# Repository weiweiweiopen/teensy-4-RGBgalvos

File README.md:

# teensy-4-RGBgalvos

Teensy 4.0 + CS42448 的 **8 通道 USB 音訊 → TDM → 8 組差分 ILDA 類比輸出**控制板。
本 repo 是目前 **RevB-P4** 設計的交接包：KiCad 專案、分析證據、製造檔、韌體與量測指南。

> 這是**可打樣、但尚未實板驗證**的版本。製造放行仍是 HOLD，請先讀 [交接總覽](docs/00-交接總覽-zhTW.md)。

## 30 秒狀態

| 項目 | 狀態 |
|---|---|
| 設計版本 | RevB-P4（110 × 100 mm、4 層、1.6 mm、337 footprints、316 SMT） |
| PCB SHA-256 | `825edcd27853183ae879091047c481432507c4003eede9e3af0c213e0eff5e42` |
| 原生檢查 | DRC 0 / unconnected 0 / ERC 0 / parity 0（另有 2 個既有 J1 絲印 warning） |
| Gerber/drill | 已回讀：545 鑽孔、1,031 unique ref/pin、14 檔 ZIP |
| 製造 | **HOLD**：U1 CS42448 缺料、DB25 實際料號、JLC 貼裝角度、實板驗證 |
| 韌體 | 已編譯、**未燒錄**；預設 gain 0.70、offset 0、未校正 |

## 從哪裡開始

| 你要做的事 | 先讀 |
|---|---|
| 5 分鐘了解整體 | [docs/00-交接總覽](docs/00-交接總覽-zhTW.md) |
| 看懂電路與訊號 | [docs/01-訊號鏈](docs/01-訊號鏈-zhTW.md) |
| 第一次上電 | [docs/02-上電與測試](docs/02-上電與測試-zhTW.md) |
| 校正八通道 | [docs/03-校正](docs/03-校正-zhTW.md) |
| 送 JLC 打樣 | [docs/04-製造與供料](docs/04-製造與供料-zhTW.md) |
| 改／燒韌體 | [docs/05-韌體](docs/05-韌體-zhTW.md) |
| 找檔案與雜湊 | [docs/06-檔案地圖](docs/06-檔案地圖-zhTW.md) |

## 專案來源與授權

- **韌體核心**：改自 [alex6679/teensy-4-usbAudio](https://github.com/alex6679/teensy-4-usbAudio)（MIT），加上 Teensyduino 1.59 的 UAC2 8 通道 patch。原始授權與出處見 [docs/05-韌體](docs/05-韌體-zhTW.md)。
- **硬體架構規劃**：由使用者以 **GPT Sol 6.1** 規劃（電源順序、隔離、watchdog、ILDA 介面）。本 repo 的 KiCad、ECO、分析與製造檔是該規劃的實作與驗證結果。
- **介面標準**：ILDA ISP-DB25 rev002（1999）：DB25 母座、X/Y 差分 10 Vpp、R/G/B/I 差分 5 Vpp、Shutter 0/+5 V、Interlock 迴路。
- **本 repo 授權**：MIT，見 [`LICENSE`](LICENSE)。datasheet、廠商圖與量測原始檔不隨 repo 散布。

## 目錄

- `hardware/revB/` — 現行設計（KiCad、分析、製造、韌體）
- `hardware/revA/` — 前一版，保留比對用
- `firmware/` — 共用 Teensy USB audio core 與早期測試 sketch
- `kicad/`、`python/` — 早期公開的概略電路與雷射路徑工具（本次未變動）
- `docs/` — 中文交接文件
- `FIRMWARE-PINS.json` — 硬體／韌體腳位對照

## 重要警告

1. 本設計**沒有**實板電源 ramp、漏電、精度、線材穩定度、滿載熱、EMC 或 USB 合規測試。分析通過不等於電氣合格。
2. `calibration.h` 的 gain/offset 是預設值，不是量測結果。
3. **預設 gain 0.70 對 X/Y 安全，對顏色超幅約 1.77 倍**：顏色應降到 0.35–0.394。詳見 [docs/03-校正](docs/03-校正-zhTW.md)。
4. 韌體有一個已知缺陷：ch ≥ 2（R/G/B/I）在加 offset 前就把負值截為 0，負向零點無法補償。詳見 [docs/03-校正](docs/03-校正-zhTW.md)。
5. 本板輸出**直接驅動 ILDA 投影機**；上電測試請用限流電源、先不接雷射、確認 interlock 與 shutter 行為。

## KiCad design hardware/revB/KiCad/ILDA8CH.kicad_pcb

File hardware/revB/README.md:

# RevB-P4：電氣保護與供電恢復ECO

**目前主工程：337 footprints、316 SMT、110×100mm、4層。** 原273個元件擺件保留；新增隔離、監測與控制電路。Native unconnected／DRC errors／ERC／parity均0，完整依據見[ECO審查](QA/power-eco-review.md)。

**製造放行仍為HOLD：J1實際MPN／機構、CS42448供料、JLC裝配角度尚待完成。** 製造資料以`manufacturing/`最新ECO draft receipt為準。

- [KiCad工程](KiCad/ILDA8CH.kicad_pro)／[PCB](KiCad/ILDA8CH.kicad_pcb)
- [原生DRC](QA/routing-drc.json)／[ERC](QA/erc.json)／[完整一致性與局部路徑audit](QA/power-eco-audit.json)
- [RevB韌體](firmware/ilda8ch_revB/ilda8ch_revB.ino)：八路USB/TDM已編譯、未燒錄。GPIO5=status、GPIO6=fresh ARM；active stop同時assert codec RESET。
- [電氣模型與邏輯回歸](QA/power-eco-verification.json)
- 新版原生preview以`preview/power-eco-*`檔為準；舊P3擺件／桌面截圖是歷史。

## 電氣修正

C18=22µF→FILT_ADC；C20=100µF→FILT_DAC。U31–U34隔開16個DAC輸入，原100k與濾波增益保留、OPA輸入新增10M回地。U35/U10依實際MCU3V3隔離ADC，上游100nF與下游4.7k配合新版27.2766／32.2766係數。U6推挽雙軌資格、U7 reset gate、U8 fresh-edge latch、U37 Schmitt shutter OE與較強下拉共同處理掉電／恢復。

In1專用GND；In2保留GND並有ECO跨接，總trace長約1938.358mm，不是純GND。native規則未降低，無新增exclusion。數值／pin-function依據不等於實板ramp、精密DC或EMC合格。

## 編輯與歷史

主PCB SHA-256：`19c24b7b0cacdd23822d85daa3e44d5104a866f5a9f83ac38824fee33554cd69`。`sources/electrical.json`／`placement.json`已同步；local symbols／footprints與datasheets隨工程。已有走線，`build_placement.py`的舊placement receipt guard刻意保留，不應直接重建覆蓋。

修正前完整快照及各輪工作證據在`eco/power-sequencing-20261025/`；P1/P2/P3與先前preflight仍保留。原始硬體及RevA是歷史入口。

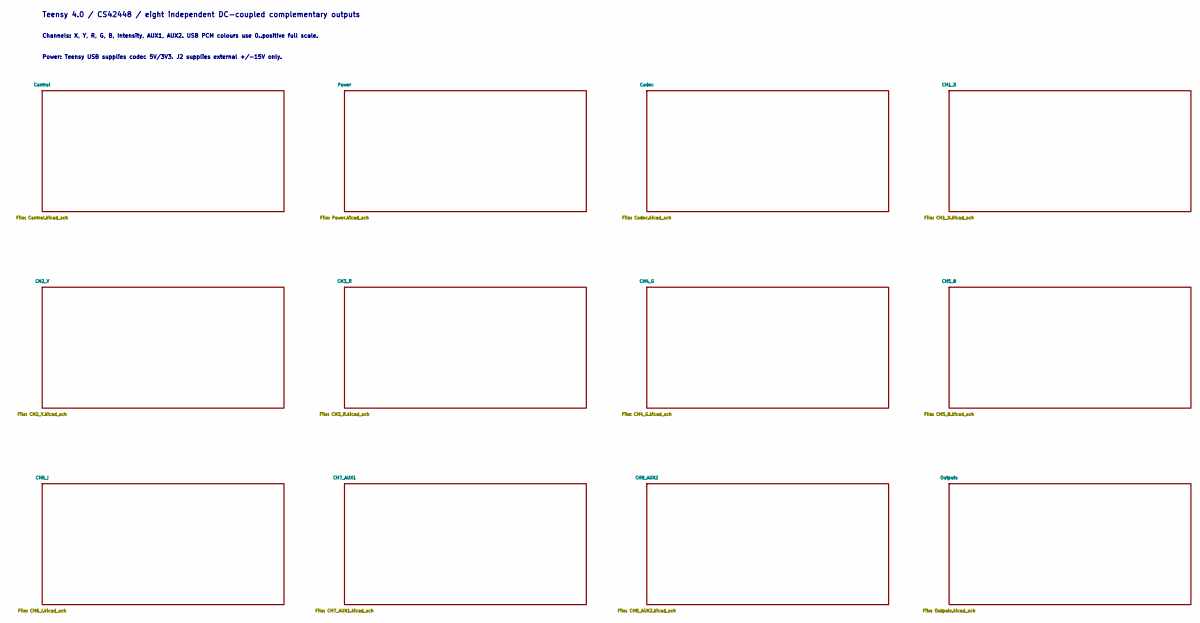
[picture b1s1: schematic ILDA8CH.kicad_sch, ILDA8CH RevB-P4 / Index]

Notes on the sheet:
Channels: X, Y, R, G, B, Intensity, AUX1, AUX2. USB PCM colours use 0..positive full scale.
Teensy 4.0 / CS42448 / eight independent DC-coupled complementary outputs
Power: Teensy USB supplies codec 5V/3V3. J2 supplies external +/-15V only.

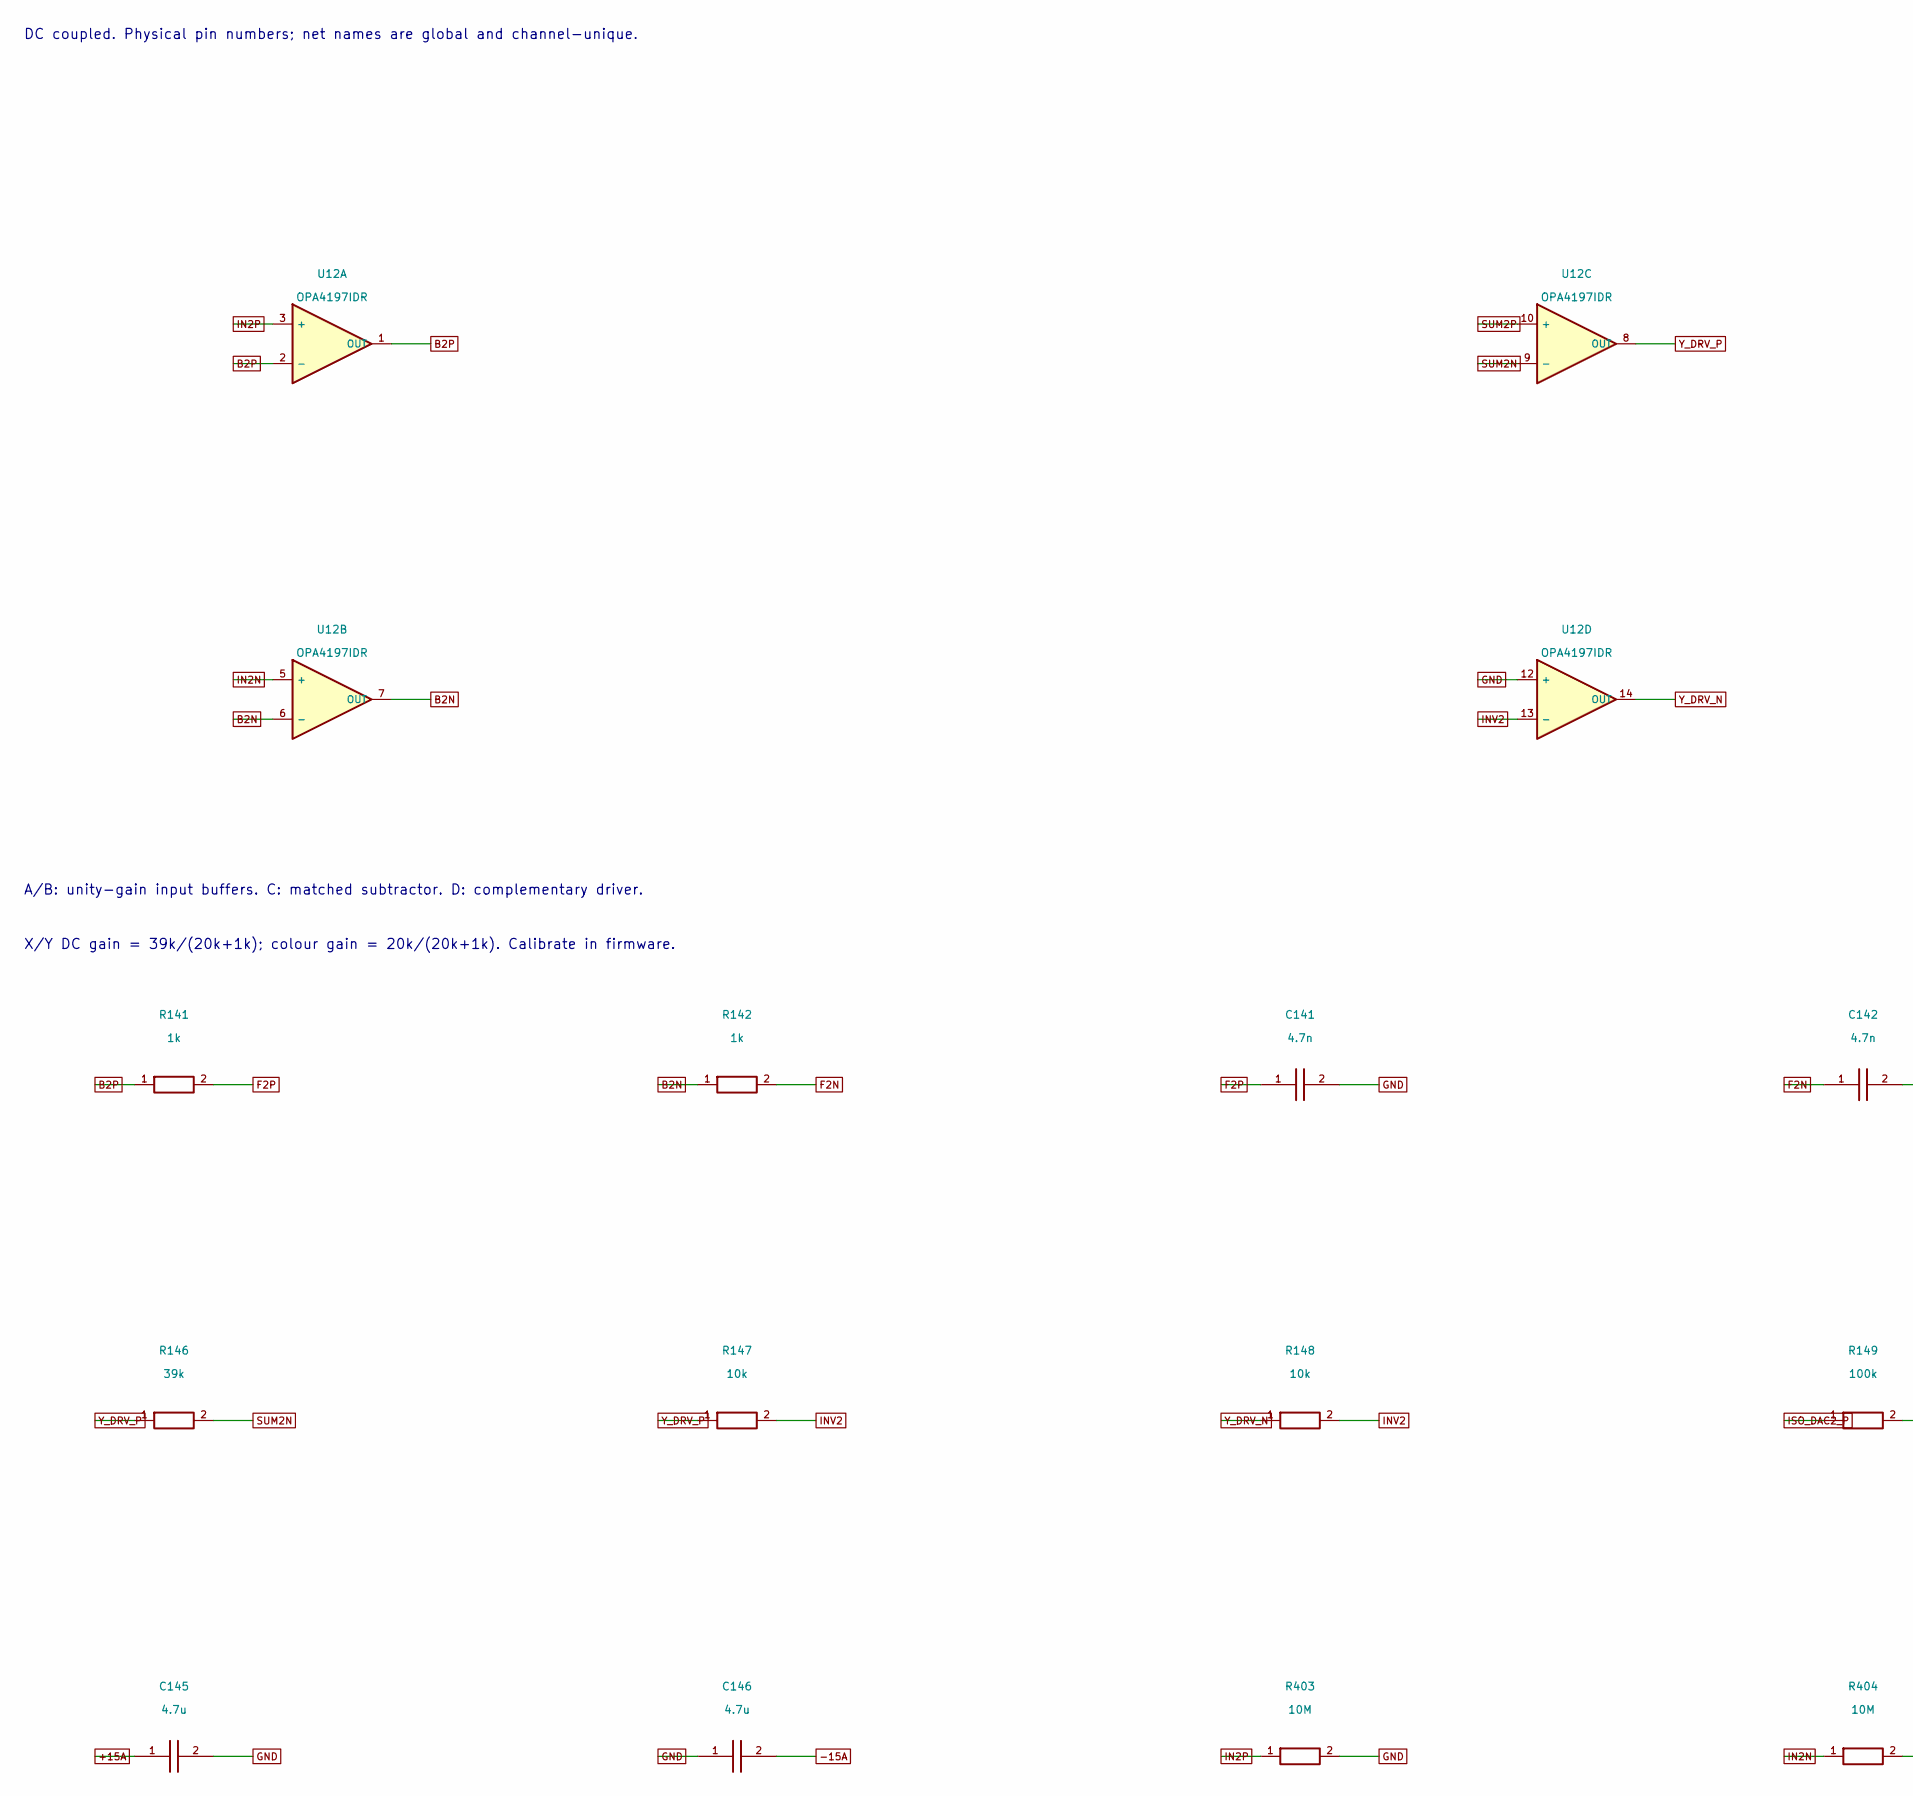
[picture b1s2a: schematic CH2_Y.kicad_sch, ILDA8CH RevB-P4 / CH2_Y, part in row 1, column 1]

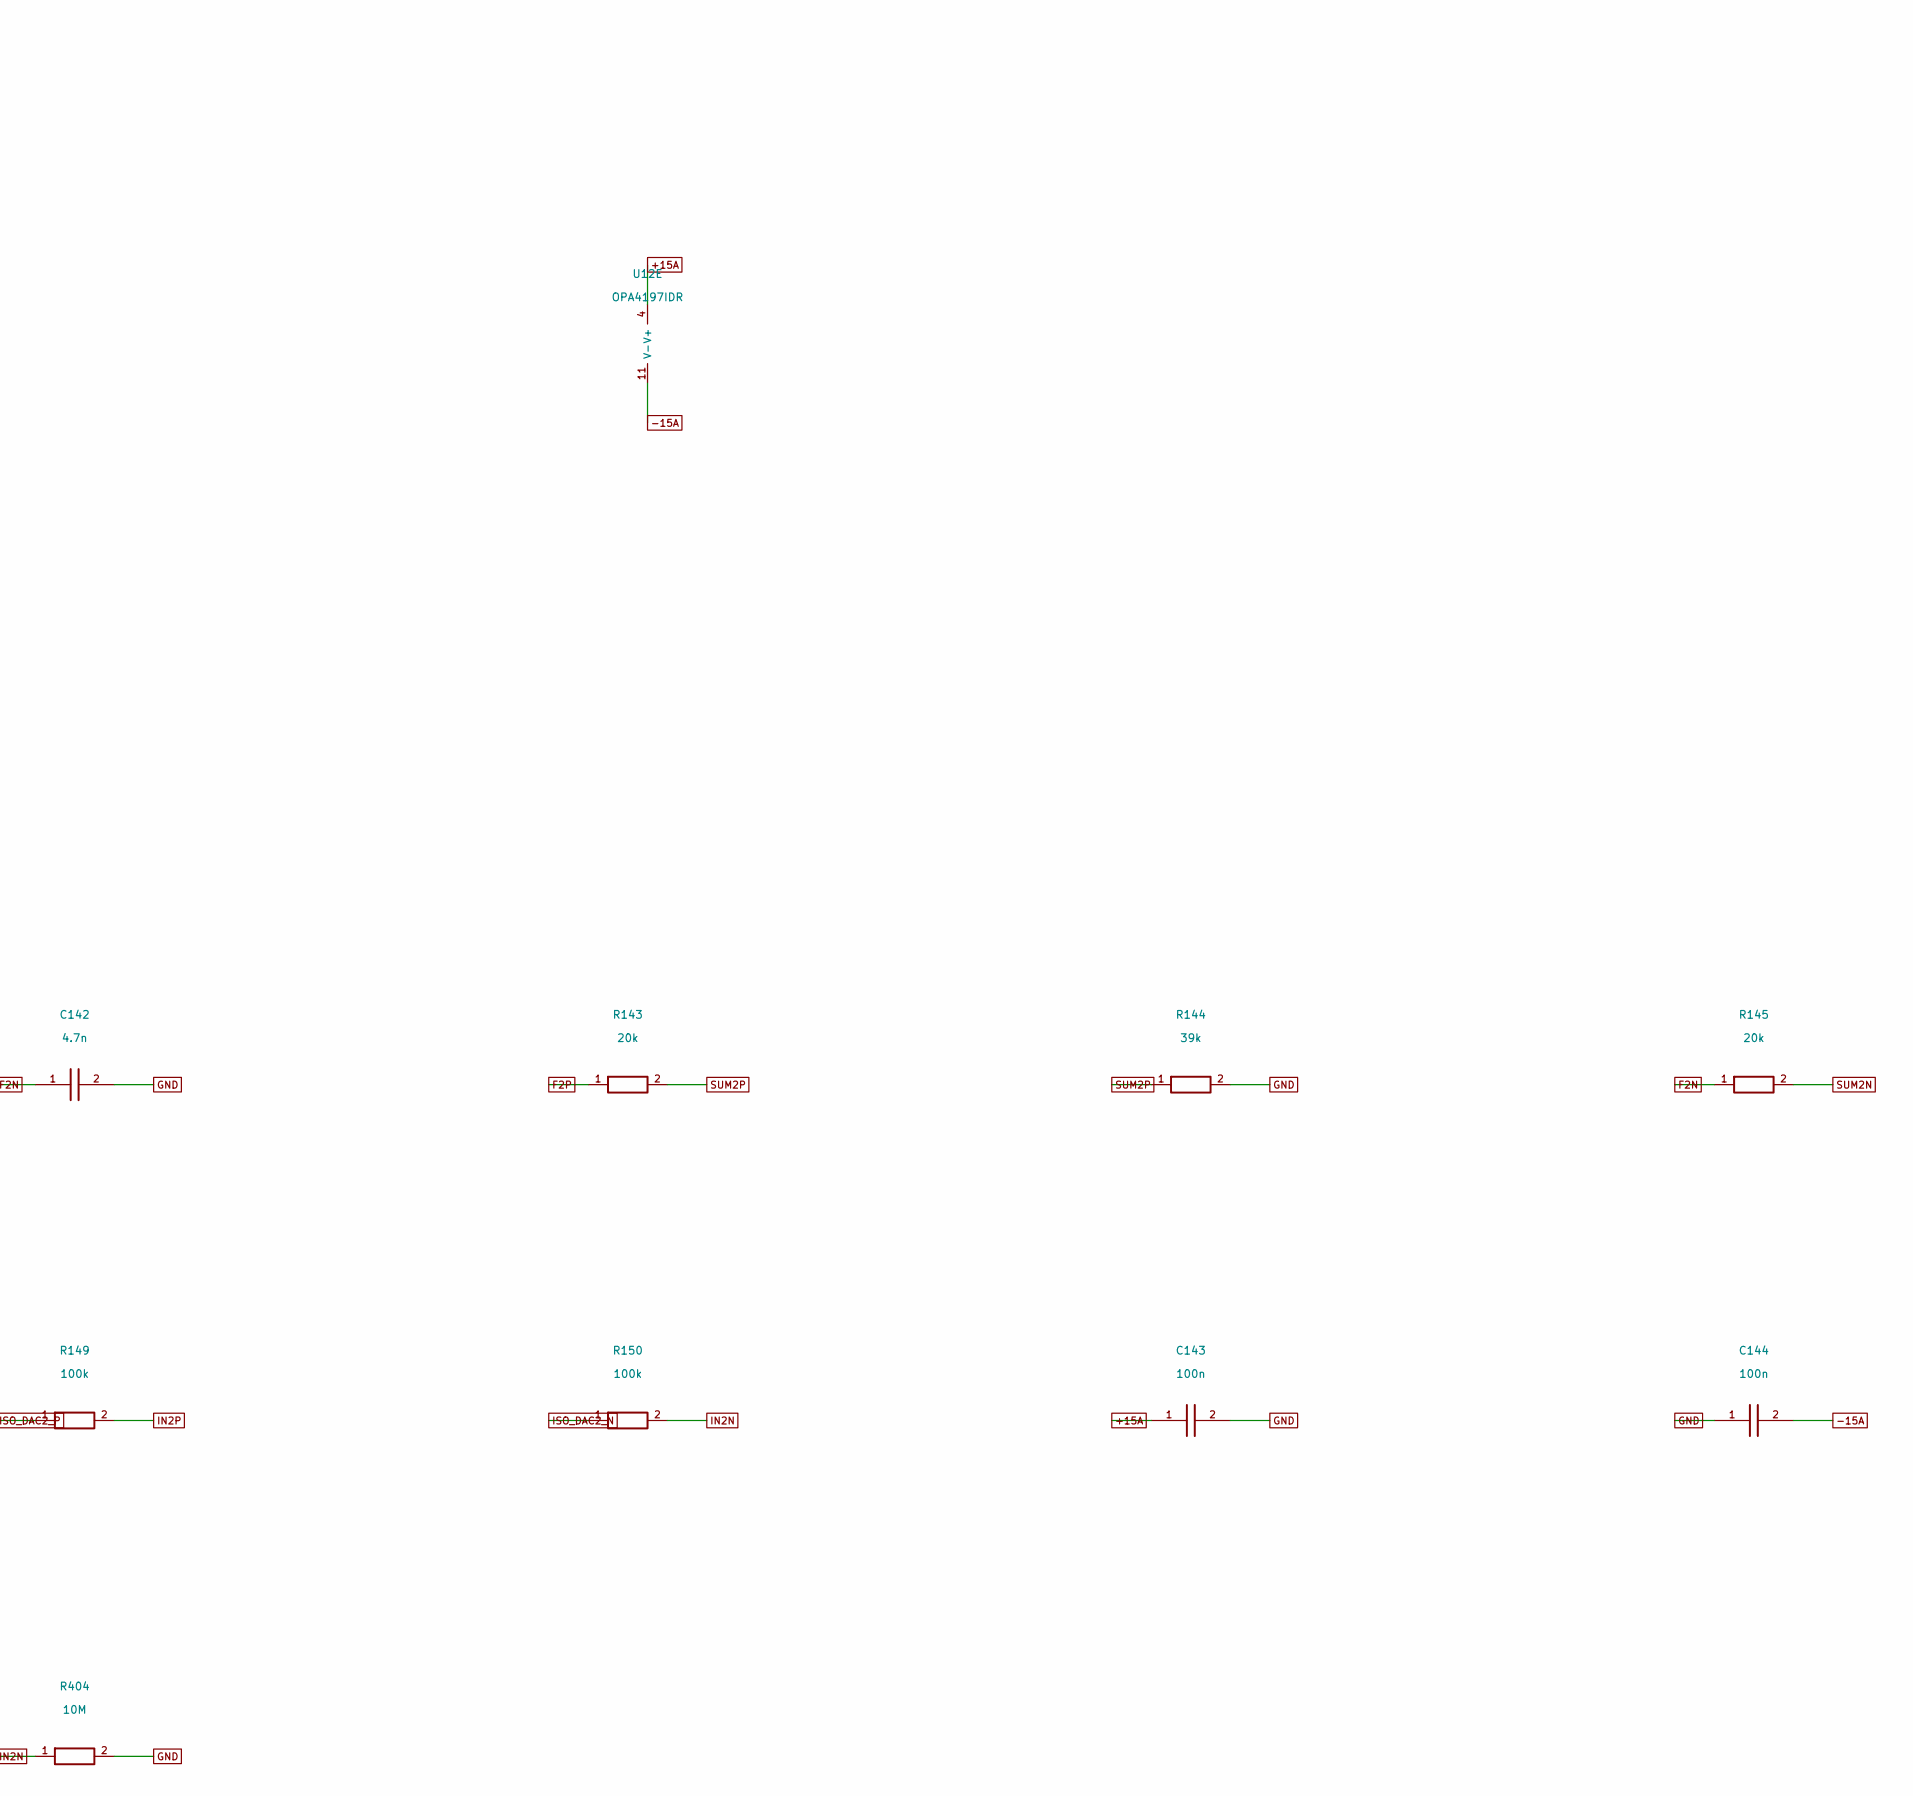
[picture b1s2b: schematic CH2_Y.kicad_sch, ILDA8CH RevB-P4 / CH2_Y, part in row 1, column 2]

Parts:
C141, C142: 4.7n; Capacitor_SMD__C_0603_1608Metric; MPN GRM1885C1H472JA01D; LCSC C85980
C143, C144: 100n; Capacitor_SMD__C_0603_1608Metric; MPN GRM188R71H104KA93D; LCSC C77055
C145, C146: 4.7u; Capacitor_SMD__C_0805_2012Metric; MPN GRM21BR61E475KA12L; LCSC C77077
R141, R142: 1k; Resistor_SMD__R_0603_1608Metric; MPN RT0603BRD071KL; LCSC C110776
R143, R145: 20k; Resistor_SMD__R_0603_1608Metric; MPN RT0603BRD0720KL; LCSC C723637
R144, R146: 39k; Resistor_SMD__R_0603_1608Metric; MPN RT0603BRD0739KL; LCSC C309652
R147, R148: 10k; Resistor_SMD__R_0603_1608Metric; MPN RT0603BRD0710KL; LCSC C95204
R149, R150: 100k; Resistor_SMD__R_0603_1608Metric; MPN RC0603FR-07100KL; LCSC C14675
R403, R404: 10M; Resistor_SMD__R_0603_1608Metric; MPN RC0603FR-0710ML; LCSC C114606
U12: OPA4197IDR; Package_SO__SOIC-14_3.9x8.7mm_P1.27mm; MPN OPA4197IDR; LCSC C2058532

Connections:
+15A: C143.1, C145.1, U12.4 (V+); also elsewhere on the board
-15A: C144.2, C146.2, U12.11 (V-); also elsewhere on the board
B2N: R142.1, U12.6 (-), U12.7 (OUT)
B2P: R141.1, U12.1 (OUT), U12.2 (-)
F2N: C142.1, R142.2, R145.1
F2P: C141.1, R141.2, R143.1
GND: C141.2, C142.2, C143.2, C144.1, C145.2, C146.1, R144.2, R403.2, R404.2, U12.12 (+); also elsewhere on the board
IN2N: R150.2, R404.1, U12.5 (+)
IN2P: R149.2, R403.1, U12.3 (+)
INV2: R147.2, R148.2, U12.13 (-)
ISO_DAC2_N: R150.1; also elsewhere on the board
ISO_DAC2_P: R149.1; also elsewhere on the board
SUM2N: R145.2, R146.2, U12.9 (-)
SUM2P: R143.2, R144.1, U12.10 (+)
Y_DRV_N: R148.1, U12.14 (OUT); also elsewhere on the board
Y_DRV_P: R146.1, R147.1, U12.8 (OUT); also elsewhere on the board

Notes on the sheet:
DC coupled. Physical pin numbers; net names are global and channel-unique.
X/Y DC gain = 39k/(20k+1k); colour gain = 20k/(20k+1k). Calibrate in firmware.
A/B: unity-gain input buffers. C: matched subtractor. D: complementary driver.

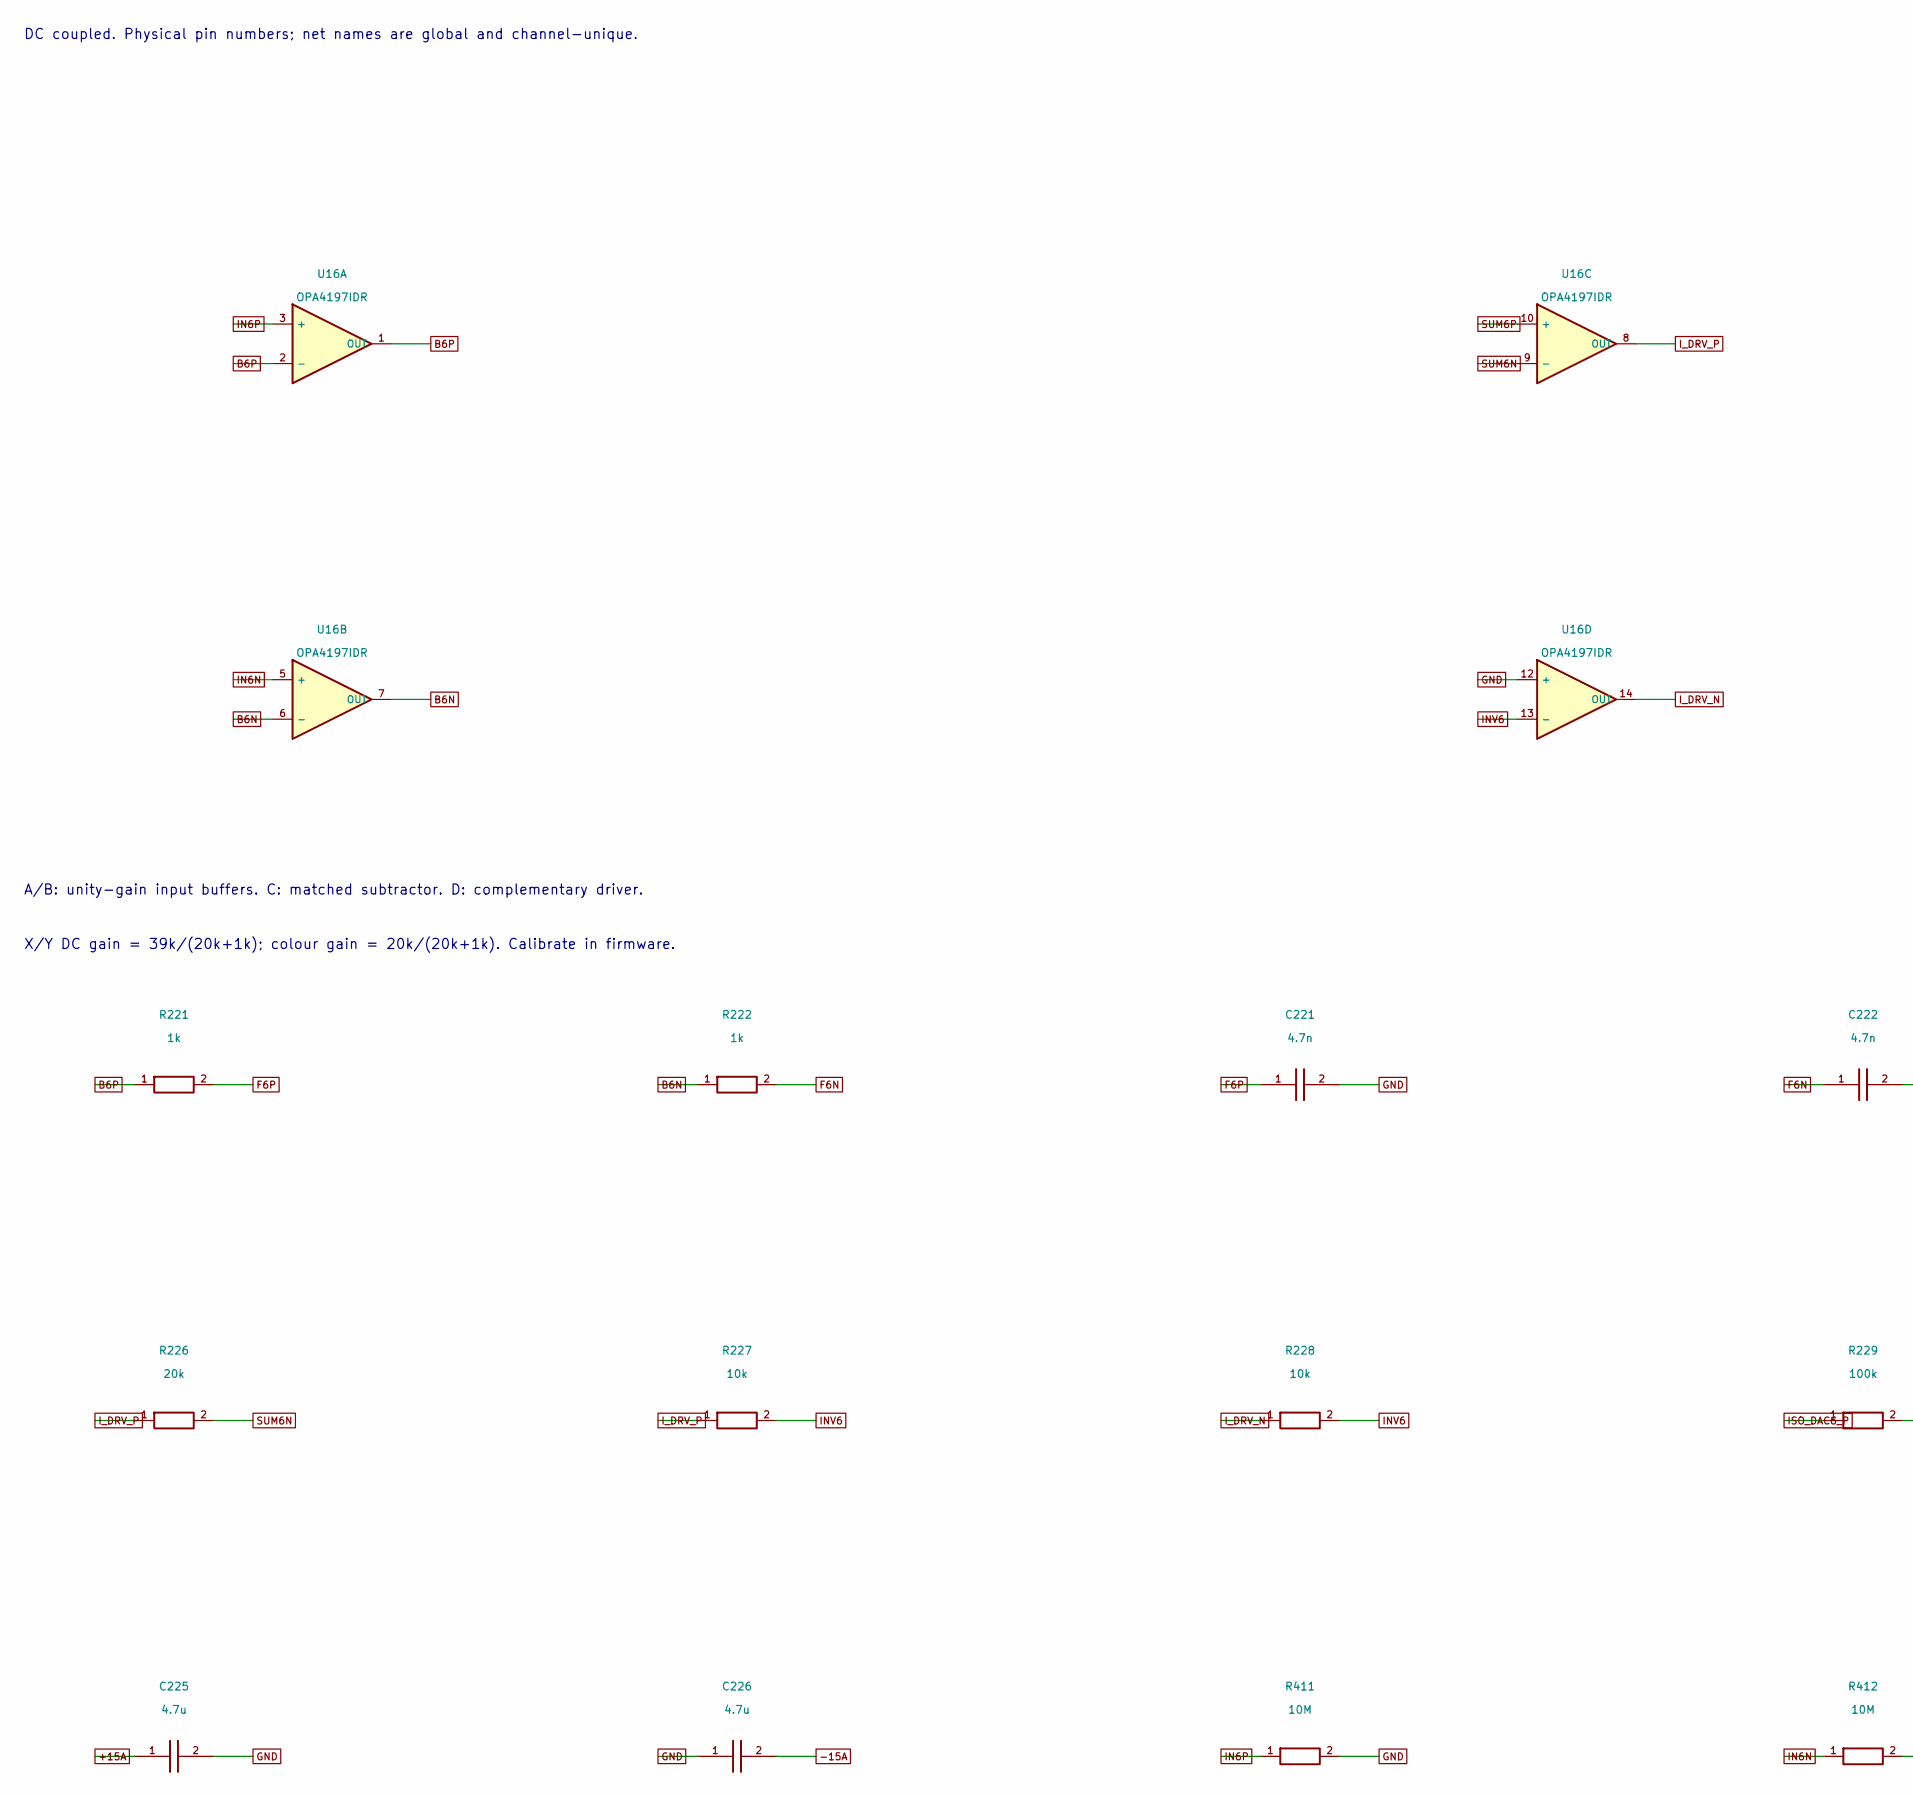
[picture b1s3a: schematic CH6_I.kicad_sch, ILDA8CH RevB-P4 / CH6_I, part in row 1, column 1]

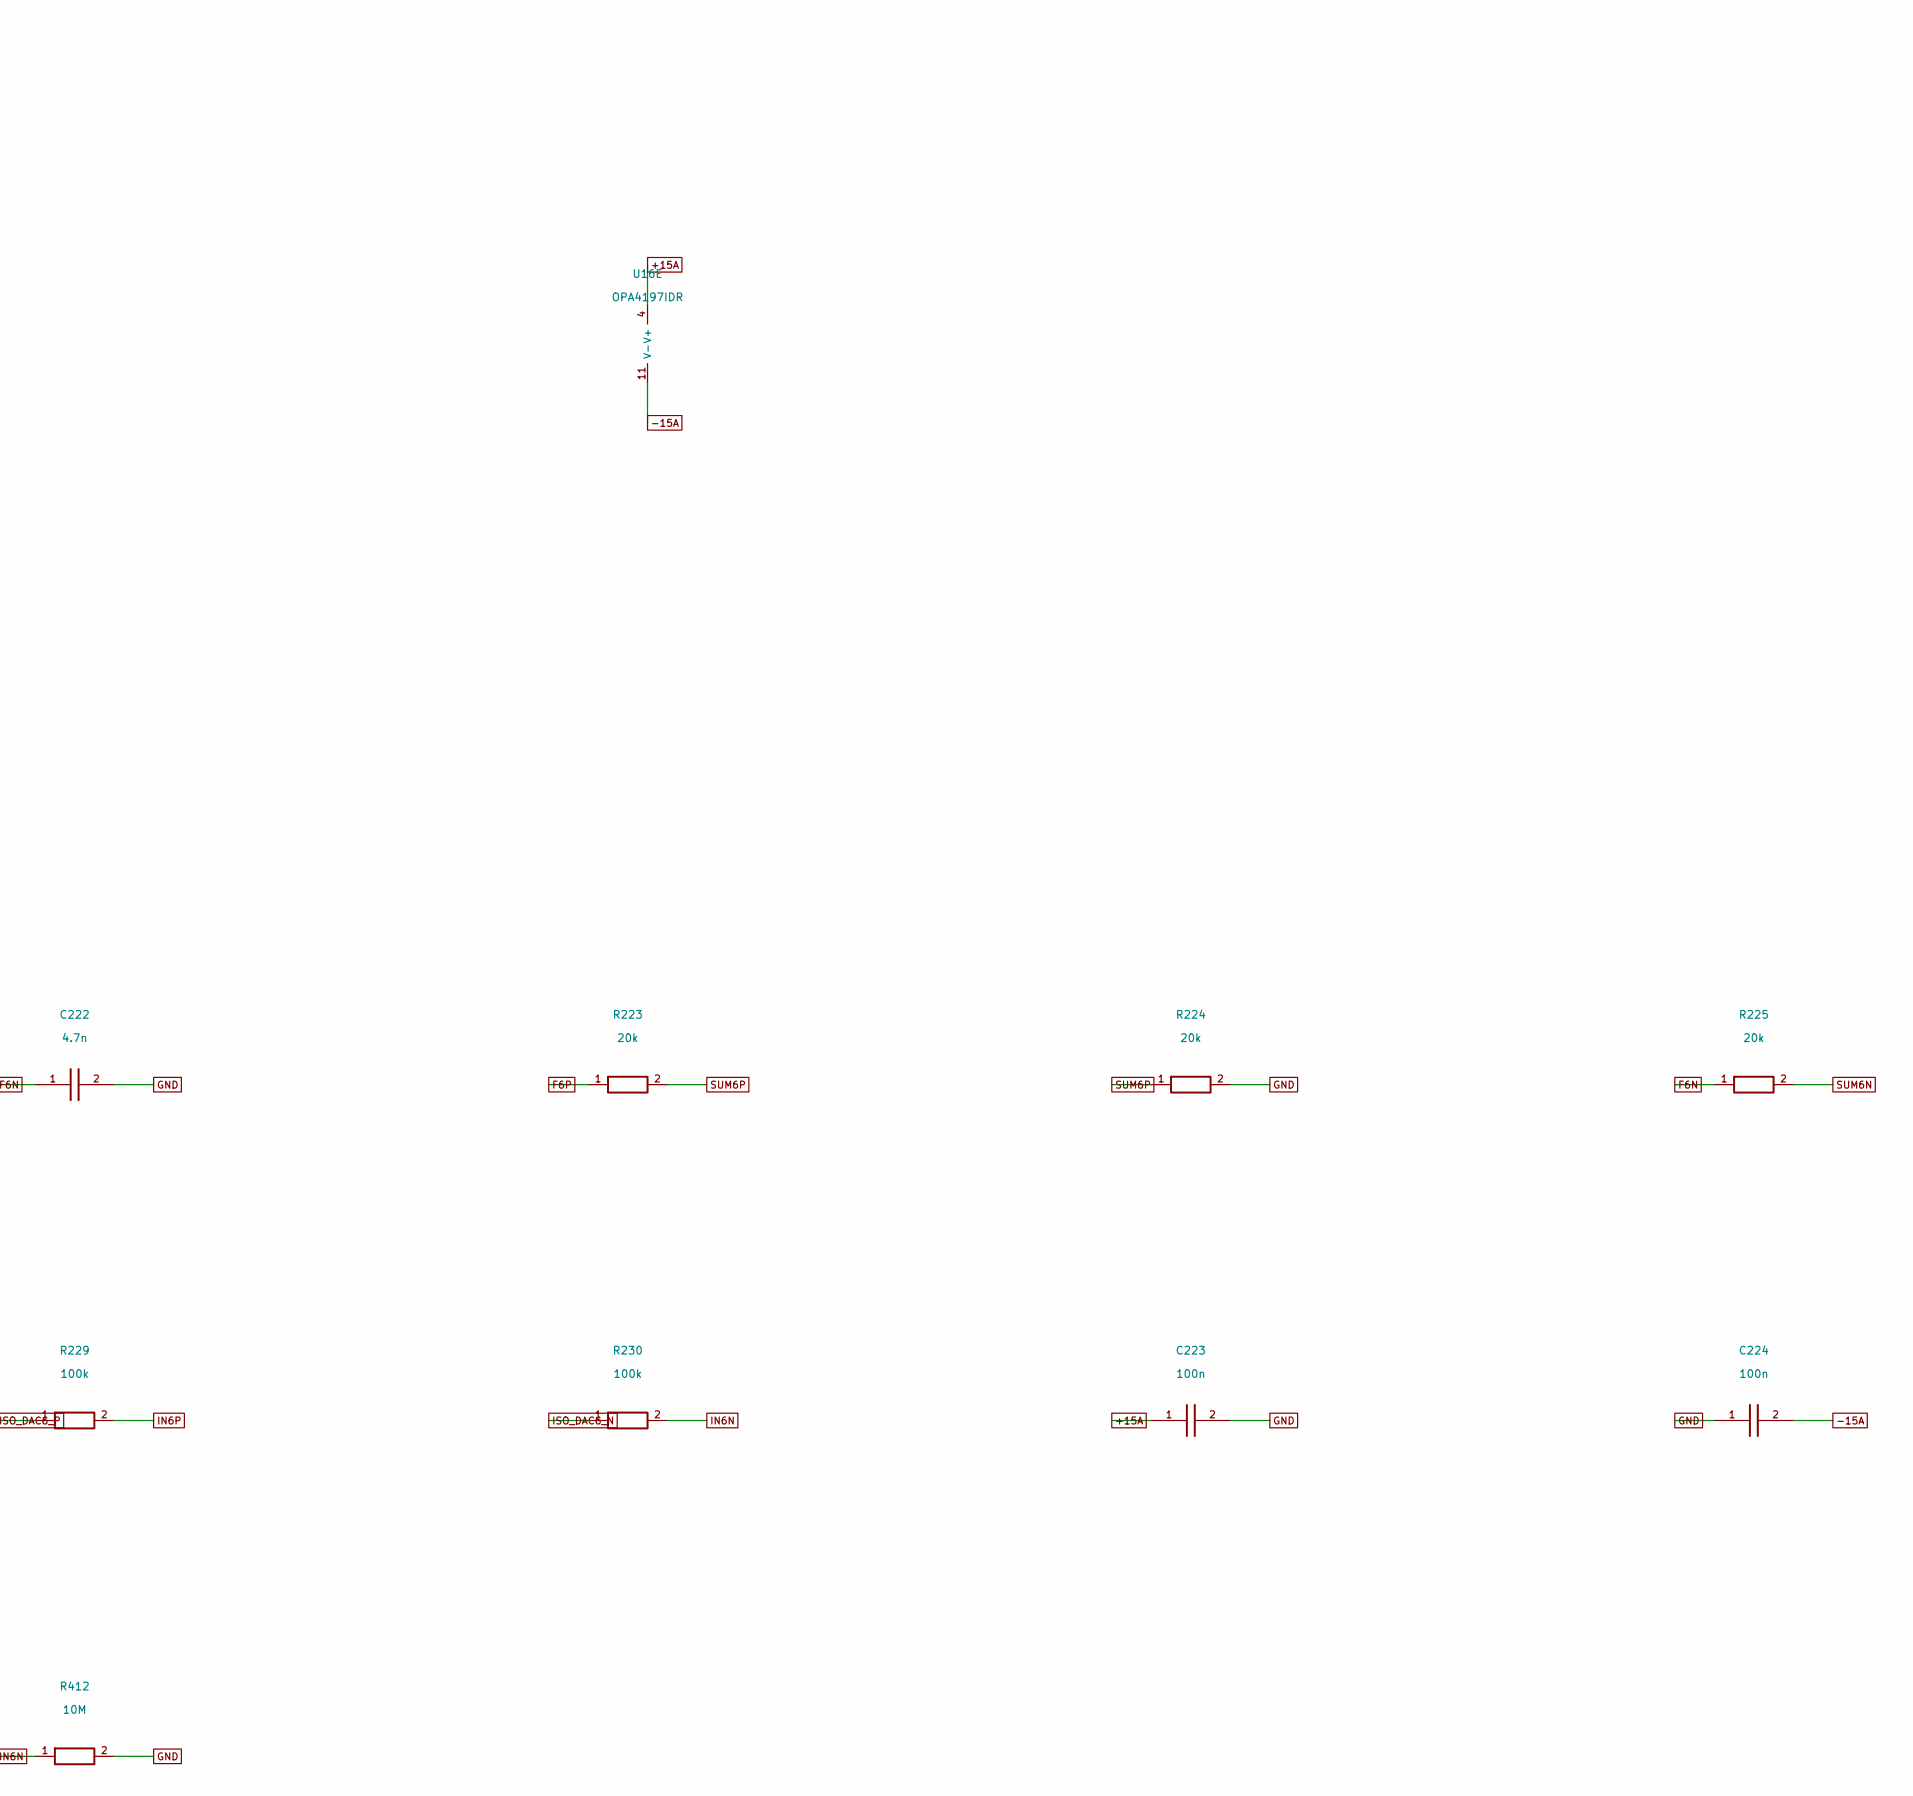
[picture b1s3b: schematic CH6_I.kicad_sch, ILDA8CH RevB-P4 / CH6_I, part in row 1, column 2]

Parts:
C221, C222: 4.7n; Capacitor_SMD__C_0603_1608Metric; MPN GRM1885C1H472JA01D; LCSC C85980
C223, C224: 100n; Capacitor_SMD__C_0603_1608Metric; MPN GRM188R71H104KA93D; LCSC C77055
C225, C226: 4.7u; Capacitor_SMD__C_0805_2012Metric; MPN GRM21BR61E475KA12L; LCSC C77077
R221, R222: 1k; Resistor_SMD__R_0603_1608Metric; MPN RT0603BRD071KL; LCSC C110776
R223, R224, R225, R226: 20k; Resistor_SMD__R_0603_1608Metric; MPN RT0603BRD0720KL; LCSC C723637
R227, R228: 10k; Resistor_SMD__R_0603_1608Metric; MPN RT0603BRD0710KL; LCSC C95204
R229, R230: 100k; Resistor_SMD__R_0603_1608Metric; MPN RC0603FR-07100KL; LCSC C14675
R411, R412: 10M; Resistor_SMD__R_0603_1608Metric; MPN RC0603FR-0710ML; LCSC C114606
U16: OPA4197IDR; Package_SO__SOIC-14_3.9x8.7mm_P1.27mm; MPN OPA4197IDR; LCSC C2058532

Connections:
+15A: C223.1, C225.1, U16.4 (V+); also elsewhere on the board
-15A: C224.2, C226.2, U16.11 (V-); also elsewhere on the board
B6N: R222.1, U16.6 (-), U16.7 (OUT)
B6P: R221.1, U16.1 (OUT), U16.2 (-)
F6N: C222.1, R222.2, R225.1
F6P: C221.1, R221.2, R223.1
GND: C221.2, C222.2, C223.2, C224.1, C225.2, C226.1, R224.2, R411.2, R412.2, U16.12 (+); also elsewhere on the board
IN6N: R230.2, R412.1, U16.5 (+)
IN6P: R229.2, R411.1, U16.3 (+)
INV6: R227.2, R228.2, U16.13 (-)
ISO_DAC6_N: R230.1; also elsewhere on the board
ISO_DAC6_P: R229.1; also elsewhere on the board
I_DRV_N: R228.1, U16.14 (OUT); also elsewhere on the board
I_DRV_P: R226.1, R227.1, U16.8 (OUT); also elsewhere on the board
SUM6N: R225.2, R226.2, U16.9 (-)
SUM6P: R223.2, R224.1, U16.10 (+)

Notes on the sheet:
DC coupled. Physical pin numbers; net names are global and channel-unique.
X/Y DC gain = 39k/(20k+1k); colour gain = 20k/(20k+1k). Calibrate in firmware.
A/B: unity-gain input buffers. C: matched subtractor. D: complementary driver.
